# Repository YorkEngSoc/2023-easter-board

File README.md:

# 2023 Easter Board

This board was created to be part of a kit for the
[York Engineering Society](https://yorksu.org/activities/view/28) to run as part
of the Easter 2023 lab.

## Credit

The design was made by [David](https://github.com/super-cow-powers) for the York
Engineering Society( Formally ShockSoc) and relesed under the BSD 3-Clause
License

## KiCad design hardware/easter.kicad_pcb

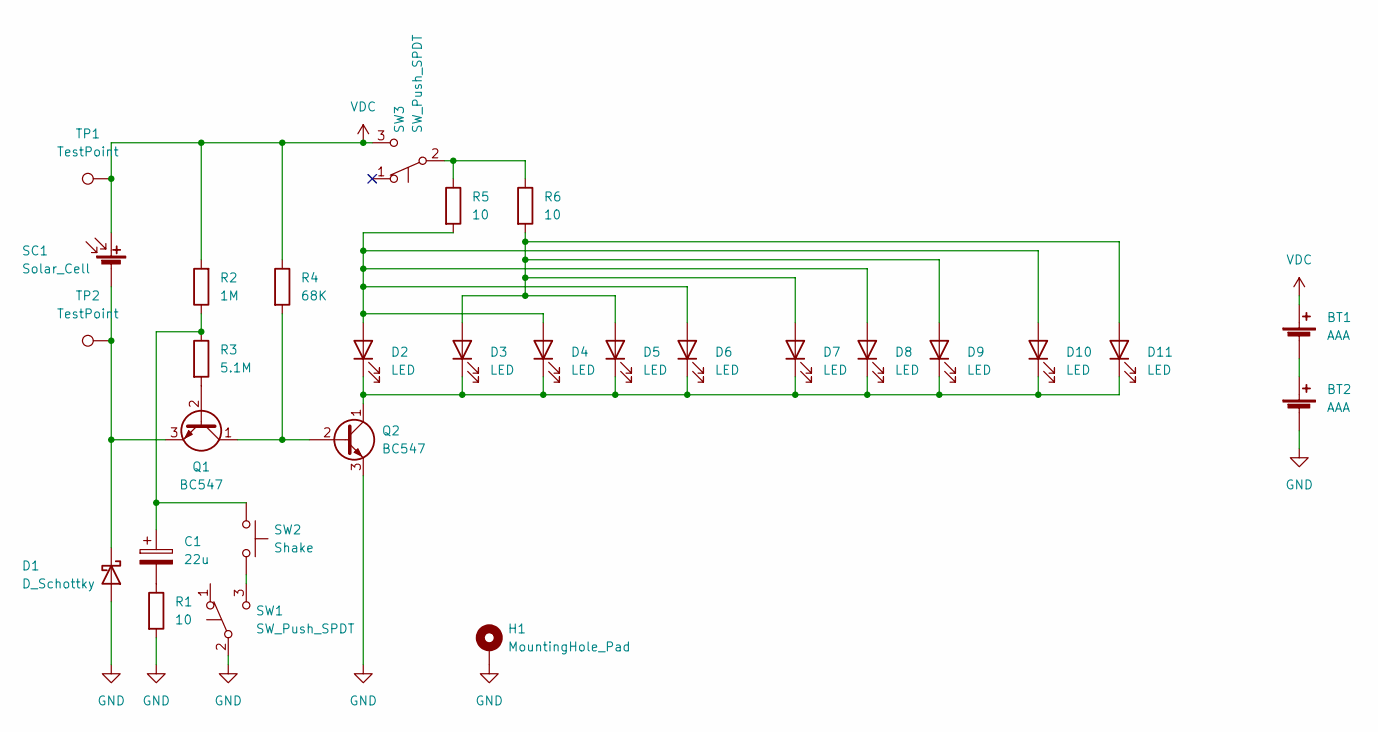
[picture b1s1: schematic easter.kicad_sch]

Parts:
BT1, BT2: AAA; MP001179
C1: 22u; CP_Radial_D6.3mm_P2.50mm
D1: D_Schottky; D_DO-41_SOD81_P10.16mm_Horizontal
D2, D3, D4, D5, D6, D7, D8, D9, D10, D11: LED; LED_D5.0mm
H1: MountingHole_Pad; MountingHole_2.2mm_M2_Pad
Q1, Q2: BC547; TO-92_Inline
R1, R5, R6: 10; R_Axial_DIN0309_L9.0mm_D3.2mm_P12.70mm_Horizontal
R2: 1M; R_Axial_DIN0309_L9.0mm_D3.2mm_P12.70mm_Horizontal
R3: 5.1M; R_Axial_DIN0309_L9.0mm_D3.2mm_P12.70mm_Horizontal
R4: 68K; R_Axial_DIN0309_L9.0mm_D3.2mm_P12.70mm_Horizontal
SC1: Solar_Cell; KXOB25-03X4F-TR
SW1, SW3: SW_Push_SPDT; SW_Slide_1P2T_CK_OS102011MS2Q
SW2: Shake; CP_Radial_D5.0mm_P2.50mm
TP1, TP2: TestPoint; TestPoint_THTPad_D2.0mm_Drill1.0mm

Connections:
GND: BT2.2 (-), D1.2 (A), H1.1, Q2.3 (E), R1.2, SW1.2 (B)
unnamed: BT1.2 (-), BT2.1 (+)
unnamed: C1.1, R2.1, R3.1, SW2.2
unnamed: C1.2, R1.1
unnamed: D1.1 (K), Q1.3 (E), SC1.2 (-), TP2.1
unnamed: D2.2 (A), D4.2 (A), D6.2 (A), D8.2 (A), D10.2 (A), R5.2
unnamed: D2.1 (K), D3.1 (K), D4.1 (K), D5.1 (K), D6.1 (K), D7.1 (K), D8.1 (K), D9.1 (K), D10.1 (K), D11.1 (K), Q2.1 (C)
unnamed: D3.2 (A), D5.2 (A), D7.2 (A), D9.2 (A), D11.2 (A), R6.2
unnamed: Q1.2 (B), R3.2
unnamed: Q1.1 (C), Q2.2 (B), R4.2
unnamed: SW1.3 (C), SW2.1
unnamed: R5.1, R6.1, SW3.2 (B)
VDC: BT1.1 (+), R2.2, R4.1, SC1.1 (+), SW3.3 (C), TP1.1

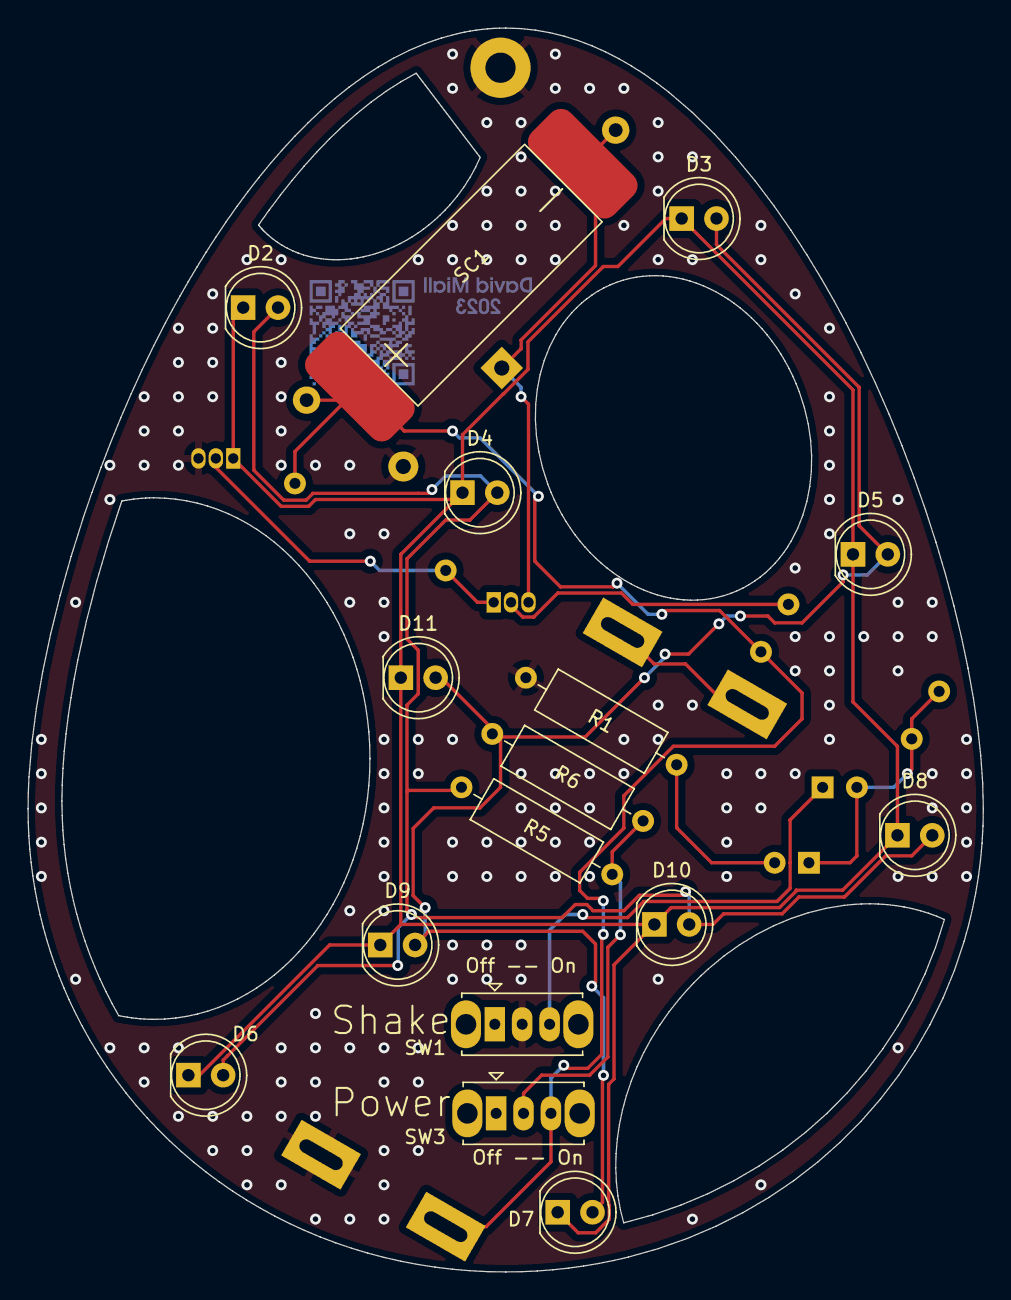
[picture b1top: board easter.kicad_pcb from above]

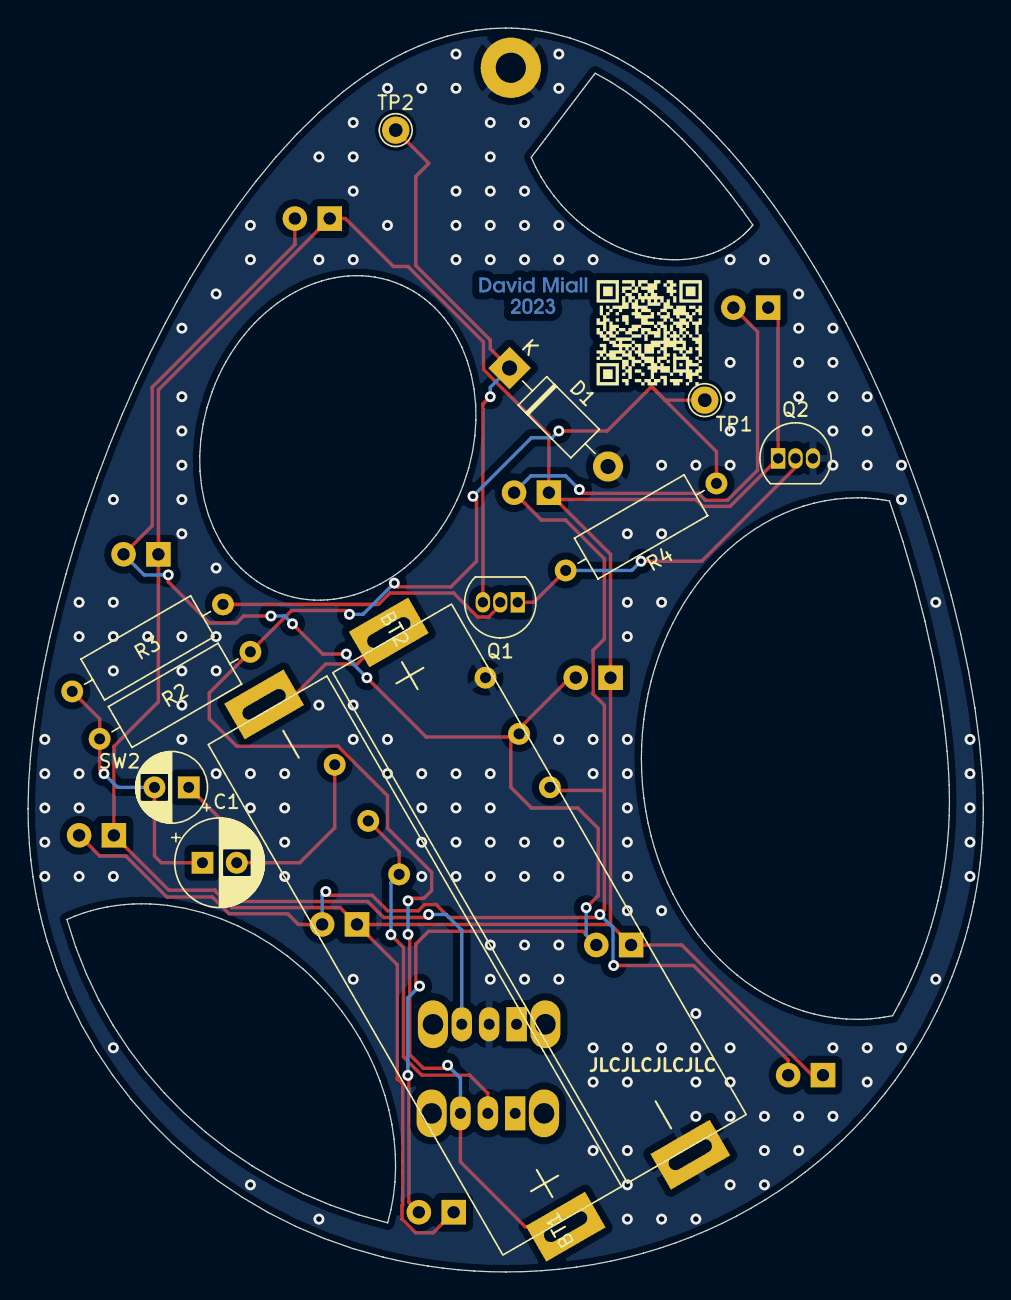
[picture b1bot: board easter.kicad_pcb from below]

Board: 2 copper layers, 69.7 x 90.7 mm, 29 parts (12 on the bottom side), 13 nets.

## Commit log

2023-02-20 Init
2023-02-21 Schematic done, placed. Routing required
2023-02-22 Finish layout. Plot gerbers
2023-02-22 Add solar test points
2023-03-05 Fix trace
2024-09-09 Removed all zip files
2024-09-09 Removed production files
2024-09-09 Moved design files
2024-09-09 Updated project to KiCad 8
2024-09-09 Moved local libs
2024-09-09 Updated links to libraries
2024-09-09 Moved SVG files to the assets folder
2024-09-09 Added render and updated README.md
